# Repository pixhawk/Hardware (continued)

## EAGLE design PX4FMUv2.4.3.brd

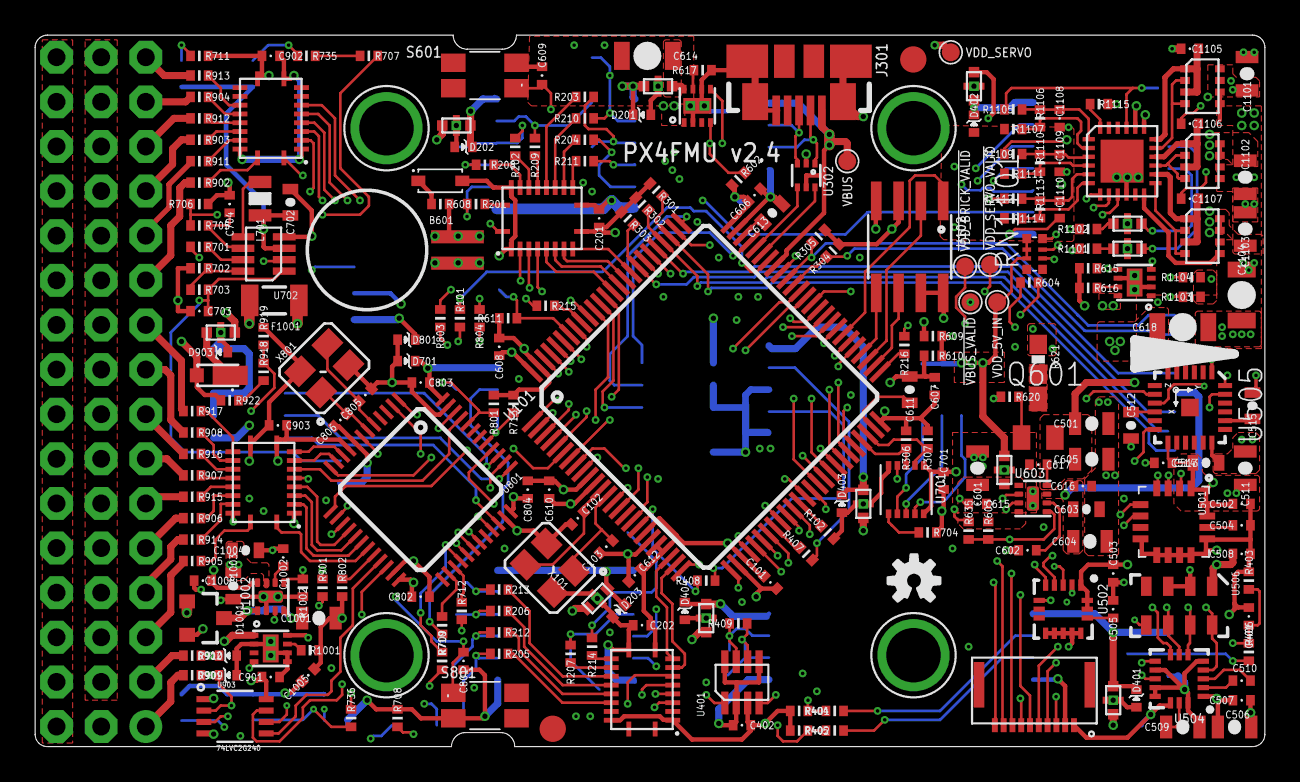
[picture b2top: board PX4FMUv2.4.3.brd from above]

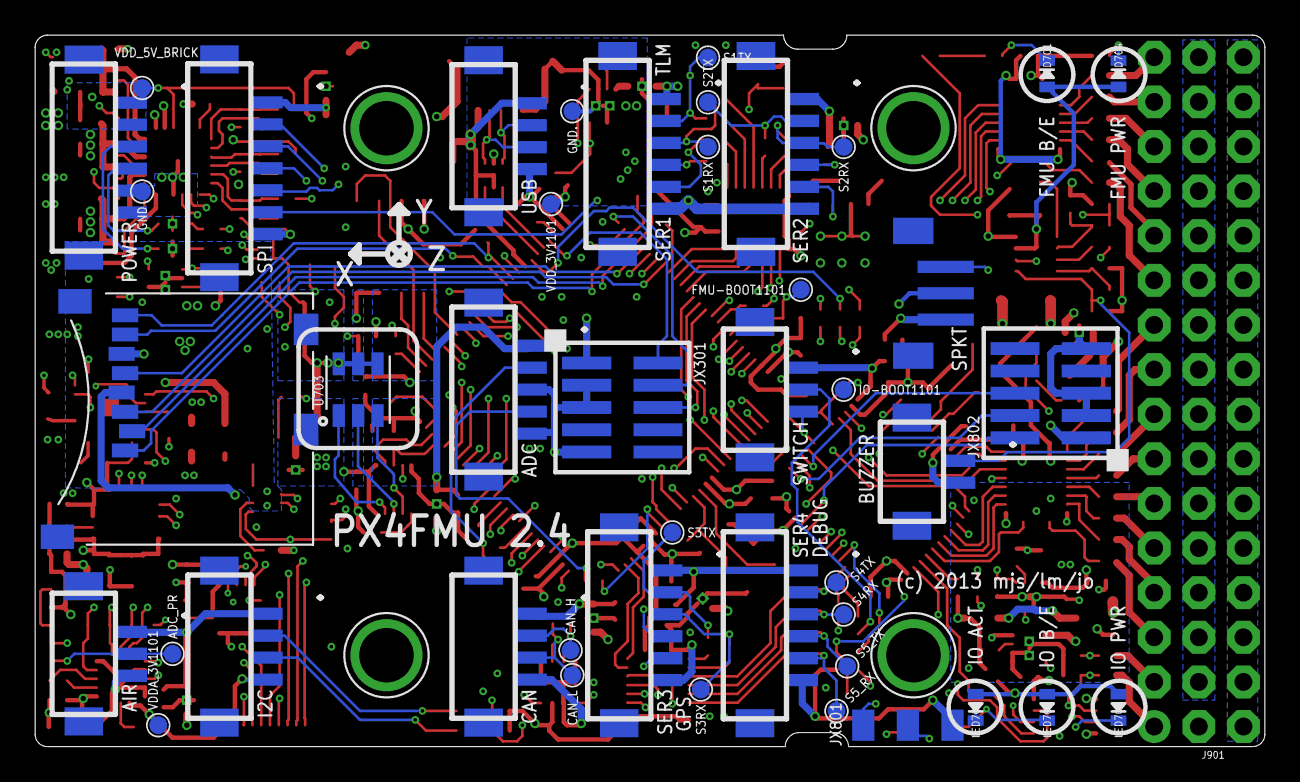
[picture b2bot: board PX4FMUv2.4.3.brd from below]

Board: 6 copper layers, 70.0 x 40.5 mm, 292 parts (45 on the bottom side), 262 nets.

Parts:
!VBUS_VALID: PAD.04; PAD.04X.04
!VDD_BRICK_VALID: PAD.04; PAD.04X.04
!VDD_SERVO_VALID: PAD.04; PAD.04X.04
ADC_PR: PAD.04; PAD.04X.04
B601: MS621FE
C101, C201, C202, C401, C402, C502, C503, C507, C508, C514, C606, C607, C608, C609, C610, C612, C615, C616, C617, C701, C801, C802, C803, C804, C901, C902, C903, C1005, C1105, C1106, C1107: 0u1; 0402-CAP
C102, C103, C805, C806: 8p; 0402-CAP
C501, C506, C509, C511: 10u/10V; 0805-CAP
C504, C505, C602, C1002: 10n; 0402-CAP
C510, C704: 0u47; 0402-CAP
C512, C513, C611, C613: 2u2; 0603-CAP
C515: 0u01; 0603-CAP
C601, C1001: 10u/25V; 0805-CAP
C603, C702, C1003: 1u; 0603-CAP
C604, C605, C1101, C1102, C1103: 22u/25V; 0805-CAP
C614, C618, C1104: 100u; 1206-CAP
C703: 5n6; 0402-CAP
C1004: 10u; 0603-CAP
C1008: 2u2; 0402-CAP
C1108, C1109, C1110: 1000p/25V; 0402-CAP
CAN_H: PAD.04; PAD.04X.04
CAN_L: PAD.04; PAD.04X.04
D201, D202, D203, D401, D402, D403, D404, D701, D801, D901, D902, D903: PESD0402-140; 0402-TVS
D602: RB751V40T1G; SOD323
D904: MSS1P4-M3; MICROSMP
D1001: PMEG2005CT; SOT23-3
F1001: 0ZCA0035FF2G; PTC-1206
FMU-BOOT1101: PAD.04; PAD.04X.04
GND, GND.: PAD.04; PAD.04X.04
IO-BOOT1101: PAD.04; PAD.04X.04
J201, J202, J203, J204, J601: DF13C-6P-1.25V
J301: 47346-0001; MOLEX-47346-0001
J302, J401, J405: DF13C-4P-1.25V
J402, J702: DF13C-3P-1.25V
J403: DF13C-7P-1.25V
J404: DF13C-5P-1.25V
J701: DF13C-2P-1.25V
J801: JST-ZH-3; JST-ZH-SMT-VERTICAL
J901: 3X16RA
JP1, JP2: FIDUCIAL1.5X3; FIDUCIAL-1.5X3
JX301, JX802: ARM_MINI_JTAG-SMT; FTSH-105-01-XXX-DV-K
JX801: HEADER-3X1BOARDEDGE-SHORT; HEADER_3X01_SMD_H_BOARD_EDGE_SHORT
L201, L202, L203, L401, L402, L403, L404, L603, L901, L1101, L1102: KNH16C104DA5TS; KYOCERA-KNH16-DA
L701: 47uH; 0805-IND
LED701, LED703: AMBER; 0603-LED
LED702, LED704: GREEN; 0603-LED
LED705: BLUE; 0603-LED
M3_MOUNT1101, M3_MOUNT1102, M3_MOUNT1103, M3_MOUNT1104: MOUNT-HOLE3.1MM; MOUNT-HOLE3.1
OSHW_LOGO: OSHW-LOGOS; OSHW-LOGO-S
Q601: MMBT3906LT1SMD; SOT23-BEC
R101: 470R; 0402-RES
R102, R603, R611, R615, R702, R704, R801, R802, R901, R1002: 10K; 0402-RES
R201, R202, R203, R204, R205, R206, R207, R208, R209, R210, R211, R212, R213, R214, R215, R216, R404, R405, R409: 120R; 0402-RES
R301, R302, R303, R304, R305, R703, R1001: 100K; 0402-RES
R306, R307, R401, R402, R713: 1K5; 0402-RES
R403, R406, R407, R408, R609, R610, R918, R919, R922, R1101, R1102: 10K/0.1%; 0402-RES
R602, R604, R1103, R1104: 1M; 0402-RES
R608: 1K; 0402-RES
R616: 25K5; 0402-RES
R617, R706: 16K5; 0402-RES
R620: 1K8; 0402-RES
R621: 10R; 0603-RES
R635: DNP/10K; 0402-RES
R701: 9K09; 0402-RES
R705, R1105, R1109, R1112: 453K; 0402-RES
R707, R708, R709, R711, R712, R735, R736, R803, R804, R902, R903, R904, R905, R906, R907, R908, R909, R910, R911, R912, R913, R914, R915, R916, R917: 220R; 0402-RES
R710: 68R; 0402-RES
R1106, R1110, R1113: 56K; 0402-RES
R1107, R1111, R1114: 105K; 0402-RES
R1115: 0R; 0402-RES
RN1101: 1M; EXB28V
S1RX, S1TX, S2RX, S2TX, S3RX, S3TX, S4RX, S4TX, S5_RX, S5_TX: PAD.04; PAD.04X.04
S601, S801: RESET; EVQP7J01K
U101: STM32F4X7VX; TQFP100
U102: FM25V01; SO08
U201, U202, U901, U902: TXS0108QFN20; QFN20-RGY
U301: 2908-05WB-MG; MICROSD
U302: NUF2042XV6; SOT563-6
U401: MAX3051; SOT23-8
U501: L3GD20; L3G4200DH-MAN
U502: L3GD20H; LGA-16L
U504: LSM303D; LGA-16L
U505: MPU-6000; QFN-24
U506: MS5611-01BA
U601, U602: BQ24315; QFN8-DSG
U603, U1002: MIC5332; MLF-8-EPAD
U701: TCA62724FMG; SON10
U702: LT3469; SOT23-8
U703: LRTB GFTG-T7AW-1+V7A7-29+R5T9-49-L; 6-PLCC
U801: STM32F10XCXT6; TQFP48
U903: 74LVC2G240; TSSOP8_SOT505-2
U1001: BQ24313; QFN8-DSG
U1101: LTC4417; MO-220
U1102, U1103, U1104: NTHD4102PT1G; 1206-8
VBUS: PAD.04; PAD.04X.04
VDDA_3V1101: PAD.04; PAD.04X.04
VDD_3V1101, VDD_5V_BRICK, VDD_5V_IN: PAD.04; PAD.04X.04
VDD_SERVO: PAD.04; PAD.04X.04
X101, X801: 3.2x2.5 mm / 24 MHz / 15 ppm; OSCILLATOR-3.2X2.5
X503: 0512811094; 51281-1094

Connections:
!ACCEL_MAG_CS: U101.9, U504.8, X503.6
!BARO_CS: U101.88, U506.5
!FMU-LED_AMBER: R707.P$1, U101.43
!FRAM_CS: U101.57, U102.1
!GYRO_CS: U101.7, U501.5, U502.5, X503.7
!IO-LED_AMBER: R709.P$1, U801.28
!IO-LED_BLUE: R712.P$1, U801.27
!IO-LED_SAFETY: R710.P$2, U801.26
!MPU_CS: U101.17, U505.8
!SBUS_OUTPUT_EN: U801.40, U903.7
!SPI_EXT_NSS: J403.5, U101.3
!VBUS_VALID: !VBUS_VALID.P$1, RN1101.2, U101.15, U1101.P$9
!VDD_5V_HIPOWER_OC: R602.P$1, U101.41, U601.4
!VDD_5V_PERIPH_EN: R615.P$1, U101.67, U601.5, U602.5
!VDD_5V_PERIPH_OC: R604.P$1, U101.46, U602.4
!VDD_BRICK_VALID: !VDD_BRICK_VALID.P$1, RN1101.4, U101.91, U1101.P$7
!VDD_SERVO_VALID: !VDD_SERVO_VALID.P$1, RN1101.3, U101.93, U1101.P$8
ACCEL_DRDY: U101.90, U504.11, X503.3
ALARM: R701.P$2, U101.77
BATT_CURRENT_SENS: R1101.P$1, U101.26
BATT_CURRENT_SENS_PROT: J601.3, L1101.P$1, R1104.P$1
BATT_VOLTAGE_SENS: R1102.P$1, U101.25
BATT_VOLTAGE_SENS_PROT: J601.4, L1102.P$1, R1103.P$1
CAN1_RX: U101.81, U401.4
CAN1_TX: U101.82, U401.1
CAN2_RX: R216.P$1, U101.51
CAN2_TX: R215.P$1, U101.92
CAN_H: CAN_H.P$1, J405.2, R409.P$1, U401.7
CAN_L: CAN_L.P$1, J405.3, R409.P$2, U401.6
FMU-!RESET: C609.P$2, R635.P$1, S601.A1, U101.14, U603.3, U701.4
FMU-BOOT0: FMU-BOOT1101.P$1, R611.P$2, U101.94
FMU-CH1: U101.45, U901.7
FMU-CH1-PROT: J901.46, R913.P$2
FMU-CH2: U101.44, U901.6
FMU-CH3: U101.42, U901.5
FMU-CH4: U101.40, U901.4
FMU-CH5: U101.60, U901.3
FMU-CH6: U101.61, U901.1
FMU-CH6-PROT: J901.31, R902.P$2
FMU-I2C1_SCL: R401.P$1, R404.P$1, U101.95
FMU-I2C1_SDA: R402.P$1, R405.P$1, U101.96
FMU-I2C2_SCL: R306.P$1, U101.47, U701.3
FMU-I2C2_SDA: R307.P$1, U101.48, U701.2
FMU-SWCLK: JX301.4, U101.76
FMU-SWDIO: JX301.2, U101.72
FMU-SWO: JX301.6, U101.89
FMU-UART4_RX: U101.24, U202.8
FMU-UART4_TX: U101.23, U202.9
FMU-UART7_RX: U101.38, U202.4
FMU-UART7_TX: U101.39, U202.5
FMU-UART8_RX: U101.97, U202.6
FMU-UART8_TX: U101.98, U202.7
FMU-USART2_CTS: U101.84, U201.9
FMU-USART2_RTS: U101.85, U201.8
FMU-USART2_RX: U101.87, U201.6
FMU-USART2_TX: U101.86, U201.7
FMU-USART3_CTS: U101.58, U201.3
FMU-USART3_RTS: U101.59, U201.1
FMU-USART3_RX: U101.56, U201.4
FMU-USART3_TX: U101.55, U201.5
FMU-VDD_3V3: C101.P$1, C201.P$1, C202.P$1, C402.P$1, C603.P$1, C604.P$1, C606.P$1, C607.P$1, C608.P$1, C610.P$1, C612.P$1, C616.P$1, C701.P$1, C902.P$1, D602.A, JX301.1, R301.P$2, R302.P$2, R303.P$2, R304.P$2, R305.P$2, R306.P$2, R307.P$2, R401.P$2, R402.P$2, R602.P$2, R604.P$2, U101.11, U101.19, U101.21, U101.22, U101.28, U101.50, U101.75, U101.100, U102.3, U102.7, U102.8, U201.2, U201.10, U201.19, U202.2, U202.10, U202.19, U301.4, U401.3, U603.7, U701.1, U701.10, U901.2, U901.10, U901.19, VDD_3V1101.P$1
FMU-VDD_5V5: C601.P$1, C615.P$1, L603.P$2, R603.P$1, U603.1, U603.4
FMU_AUX_ADC1: R408.P$1, U101.18
FMU_AUX_ADC1_PROT: J404.4, R408.P$2
FMU_AUX_ADC2: R407.P$1, U101.33
FMU_AUX_ADC2_PROT: J404.2, R407.P$2
FRAM_MISO: U101.53, U102.2
FRAM_MOSI: U101.54, U102.5
FRAM_SCK: U101.52, U102.6
GND: B601.2, C101.P$2, C102.P$2, C103.P$1, C201.P$2, C202.P$2, C401.P$2, C402.P$2, C501.P$2, C502.P$2, C503.P$2, C504.P$2, C505.P$2, C506.P$2, C507.P$2, C508.P$2, C509.P$2, C511.P$2, C512.P$2, C513.P$2, C514.P$2, C515.P$2, C601.P$2, C602.P$1, C603.P$2, C604.P$2, C605.P$2, C606.P$2, C607.P$2, C608.P$2, C609.P$1, C610.P$2, C611.P$2, C612.P$2, C613.P$2, C614.P$2, C615.P$2, C616.P$2, C617.P$2, C618.P$2, C701.P$2, C702.P$2, C703.P$2, C704.P$2, C801.P$1, C802.P$2, C803.P$2, C804.P$2, C805.P$2, C806.P$1, C901.P$2, C902.P$2, C903.P$2, C1001.P$2, C1002.P$2, C1003.P$2, C1004.P$2, C1005.P$2, C1008.P$2, C1101.P$2, C1102.P$2, C1103.P$2, C1104.P$2, C1105.P$2, C1106.P$2, C1107.P$2, C1108.P$2, C1109.P$2, C1110.P$2, D201.A, D202.A, D203.A, D401.A, D402.A, D403.A, D404.A, D701.A, D801.A, D901.A, D902.A, D903.A, GND.P$1, GND..P$1, J201.6, J202.6, J203.6, J204.6, J301.GND, J301.GND1, J301.GND2, J301.GND3, J301.GND4, J302.4, J401.4, J402.3, J403.7, J404.3, J404.5, J405.4, J601.5, J601.6, J701.2, J801.P$2, J901.3, J901.6, J901.9, J901.12, J901.15, J901.18, J901.21, J901.24, J901.27, J901.30, J901.33, J901.36, J901.39, J901.42, J901.45, J901.48, JX301.3, JX301.5, JX301.9, JX801.3, JX802.3, JX802.5, JX802.9, L201.P$3, L201.P$4, L201.P$5, L202.P$3, L202.P$4, L202.P$5, L203.P$3, L203.P$4, L203.P$5, L401.P$3, L401.P$4, L401.P$5, L402.P$3, L402.P$4, L402.P$5, L403.P$3, L403.P$4, L403.P$5, L404.P$3, L404.P$4, L404.P$5, L603.P$3, L603.P$4, L603.P$5, L901.P$3, L901.P$4, L901.P$5, L1101.P$3, L1101.P$4, L1101.P$5, L1102.P$3, L1102.P$4, L1102.P$5, R102.P$2, R403.P$1, R610.P$2, R611.P$1, R615.P$2, R616.P$2, R617.P$2, R621.1, R702.P$2, R704.P$1, R706.P$2, R708.P$1, R711.P$1, R713.P$2, R801.P$2, R802.P$2, R919.P$1, R1001.P$1, R1002.P$1, R1103.P$2, R1104.P$2, R1107.P$2, R1111.P$2, R1114.P$2, R1115.P$1, S601.B3, S801.B3, U101.10, U101.20, U101.27, U101.74, U101.99, U102.4, U201.11, U202.11, U301.6, U302.2, U401.2, U401.5, U401.8, U501.8, U501.9, U501.10, U501.11, U501.12, U501.13, U502.9, U502.10, U502.11, U502.12, U502.13, U504.5, U504.10, U504.12, U504.13, U504.16, U505.1, U505.18, U506.2, U506.3, U601.2, U601.6, U601.GND, U601.P$2, U601.P$3, U602.2, U602.6, U602.GND, U602.P$2, U602.P$3, U603.2, U603.GND, U701.5, U702.4, U801.8, U801.23, U801.35, U801.47, U901.11, U902.11, U903.1, U903.4, U1001.2, U1001.5, U1001.6, U1001.GND, U1001.P$2, U1001.P$3, U1002.2, U1002.GND, U1101.P$10, U1101.P$25, X101.2, X101.4, X503.2, X801.2, X801.4
GPIO_EXT_1: J403.6, U101.8
GYRO_DRDY: U101.35, U501.6, U502.6, X503.5
IO-!RESET: C801.P$2, S801.A1, U801.7, U1002.3
IO-!VDD_SERVO_IN_FAULT: U801.38, U1001.4
IO-BOOT0: IO-BOOT1101.P$1, R801.P$1, U801.44
IO-BOOT1: R802.P$1, U801.20
IO-CH1: U801.10, U902.9
IO-CH1-PROT: J901.28, R917.P$2
IO-CH2: U801.11, U902.8
IO-CH3: U801.45, U902.7
IO-CH4: U801.46, U902.6
IO-CH5: U801.16, U902.5
IO-CH6: U801.17, U902.4
IO-CH7: U801.18, U902.3
IO-CH8: U801.19, U902.1
IO-CH8-PROT: J901.7, R905.P$2
IO-SWCLK: JX802.4, U801.37
IO-SWDIO: JX802.2, U801.34
IO-SWO: JX802.6, U801.39
IO-USART1_RX: J801.P$3, JX801.2, U801.31
IO-USART1_TX: JX801.1, R101.P$2, U801.30
IO-VDD_3V3: C802.P$1, C803.P$1, C804.P$1, C901.P$1, C903.P$1, C1003.P$1, C1004.P$1, D701.C, J702.1, JX802.1, U801.9, U801.24, U801.36, U801.48, U902.2, U902.10, U902.19, U903.8, U1002.7
IO-VDD_5V5: C1001.P$1, C1005.P$1, D1001.3, J901.2, LED702.A, LED703.A, LED705.A, U1002.1, U1002.4
MAG_DRDY: U101.36, U504.9, X503.4
MPU_DRDY: U101.62, U505.12
unnamed: C103.P$2, U101.13, X101.1
unnamed: C102.P$1, U101.12, X101.3
unnamed: R918.P$2, R922.P$1
unnamed: D1001.2, U1001.8
unnamed: D201.C, J201.1, L201.P$2
unnamed: C509.P$1, U504.15
unnamed: LED704.C, R711.P$2
unnamed: C613.P$1, U101.73
unnamed: LED705.C, R712.P$2
unnamed: C510.P$1, U504.2
unnamed: C602.P$2, U603.6
unnamed: C611.P$1, U101.49
unnamed: R707.P$2, R735.P$1
unnamed: J203.4, R215.P$2
unnamed: R803.P$1, U801.12
unnamed: R804.P$1, U801.13
unnamed: C510.P$2, U504.3
unnamed: C806.P$2, U801.6, X801.1
unnamed: J203.5, R216.P$2
unnamed: R1001.P$2, U1001.7
unnamed: D602.C, R608.P$2
unnamed: C805.P$1, U801.5, X801.3
unnamed: R101.P$1, U101.69
unnamed: R705.P$2, R706.P$1, U702.2
unnamed: R702.P$1, R703.P$2, U702.8
unnamed: LED701.C, R735.P$2
unnamed: C703.P$1, J701.1, R703.P$1, U702.1
unnamed: R701.P$1, U702.7
unnamed: LED702.C, R708.P$2
unnamed: C505.P$1, U502.14
unnamed: J901.10, R914.P$2
unnamed: L701.P$2, U702.5
unnamed: J401.2, R404.P$2
unnamed: R616.P$1, U602.7
unnamed: C504.P$1, U501.14
unnamed: C704.P$1, R705.P$1, U702.6
unnamed: J401.3, R405.P$2
unnamed: D902.C, R901.P$2, R910.P$1, U903.3
unnamed: R709.P$2, R736.P$1
unnamed: LED703.C, R736.P$2
unnamed: D402.C, J403.1, L402.P$2
unnamed: D401.C, J401.1, J402.1, L401.P$2
unnamed: R905.P$1, U902.20
unnamed: R914.P$1, U902.18
unnamed: R906.P$1, U902.17
unnamed: D1001.1, F1001.2
unnamed: C1108.P$1, R1105.P$2, R1106.P$1, U1101.P$1
unnamed: D404.C, J405.1, L403.P$2
unnamed: R915.P$1, U902.16
unnamed: C512.P$1, U505.10
unnamed: C515.P$1, U505.20
unnamed: R907.P$1, U902.15
unnamed: R1106.P$2, R1107.P$1, U1101.P$2
unnamed: C1109.P$1, R1109.P$2, R1110.P$1, U1101.P$3
unnamed: R1110.P$2, R1111.P$1, U1101.P$4
unnamed: J702.2, R710.P$1
unnamed: R916.P$1, U902.14
unnamed: R908.P$1, U902.13
unnamed: R917.P$1, U902.12
unnamed: R902.P$1, U901.20
unnamed: R911.P$1, U901.18
unnamed: R903.P$1, U901.17
unnamed: R912.P$1, U901.16
unnamed: R904.P$1, U901.15
unnamed: R913.P$1, U901.14
unnamed: R1113.P$2, R1114.P$1, U1101.P$6
unnamed: J901.34, R911.P$2
unnamed: C1110.P$1, R1112.P$2, R1113.P$1, U1101.P$5
unnamed: R201.P$1, U201.20
unnamed: J901.13, R906.P$2
unnamed: J901.16, R915.P$2
unnamed: J901.19, R907.P$2
unnamed: J901.22, R916.P$2
unnamed: J901.25, R908.P$2
unnamed: J901.37, R903.P$2
unnamed: J901.40, R912.P$2
unnamed: J901.43, R904.P$2
unnamed: Q601.C, R621.2
unnamed: Q601.B, R620.P$1
unnamed: R208.P$1, U201.18
unnamed: R202.P$1, U201.17
unnamed: R209.P$1, U201.16
unnamed: R203.P$1, U201.15
unnamed: R210.P$1, U201.14
unnamed: R204.P$1, U201.13
unnamed: R211.P$1, U201.12
unnamed: R207.P$1, U202.13
unnamed: R214.P$1, U202.12
unnamed: R205.P$1, U202.17
unnamed: R212.P$1, U202.16
unnamed: R206.P$1, U202.15
unnamed: R213.P$1, U202.14
unnamed: R704.P$2, U701.6
unnamed: R617.P$1, U601.7
unnamed: C1105.P$1, U1101.P$18, U1102.P$1, U1102.P$3
unnamed: D403.C, J404.1, L404.P$2
unnamed: J901.4, R910.P$2
unnamed: D203.C, J203.1, J204.1, L203.P$2
unnamed: D202.C, J202.1, L202.P$2
unnamed: L1102.P$2, R1102.P$2
unnamed: L1101.P$2, R1101.P$2
unnamed: C1002.P$1, U1002.6
unnamed: R1115.P$2, U1101.P$24
unnamed: C1106.P$1, U1101.P$16, U1103.P$1, U1103.P$3
unnamed: C1107.P$1, U1101.P$14, U1104.P$1, U1104.P$3
unnamed: U1101.P$13, U1104.P$2, U1104.P$4
unnamed: D903.C, D904.CATHODE, L901.P$1
unnamed: U1101.P$15, U1103.P$2, U1103.P$4
unnamed: U1101.P$17, U1102.P$2, U1102.P$4
OTG_DM1: J301.D-, J302.3, U302.1
OTG_DP1: J301.D+, J302.2, U302.3
OTG_FS_DM: U101.70, U302.6
OTG_FS_DP: U101.71, U302.4
PB2-BOOT1: R102.P$1, U101.37
PPM-SBUS-PROT: J901.1, R909.P$2
PPM_INPUT: D901.C, R909.P$1, U801.29, U903.2
PRESSURE_SENS: C401.P$1, R403.P$2, R406.P$1, U101.34
PRESSURE_SENS_IN: ADC_PR.P$1, J402.2, R406.P$2
RGB_LED_3: U701.9, U703.C1
RGB_LED_4: U701.8, U703.C2
RGB_LED_14: U701.7, U703.C3
RSSI_IN: R901.P$1, U801.15, U801.33
SAFETY: J702.3, R713.P$1, U801.41
SBUS_INPUT: U801.22, U903.6
SBUS_OUTPUT: U801.21, U903.5
SDIO_CK: U101.80, U301.5
SDIO_CMD: R303.P$1, U101.83, U301.3
SDIO_D0: R304.P$1, U101.65, U301.7
SDIO_D1: R305.P$1, U101.66, U301.8
SDIO_D2: R301.P$1, U101.78, U301.1
SDIO_D3: R302.P$1, U101.79, U301.2
SERIAL1_CTS: J201.4, R211.P$2
SERIAL1_RTS: J201.5, R204.P$2
SERIAL1_RX: J201.3, R203.P$2, S1RX.P$1
SERIAL1_TX: J201.2, R210.P$2, S1TX.P$1
SERIAL2_CTS: J202.4, R208.P$2
SERIAL2_RTS: J202.5, R201.P$2
SERIAL2_RX: J202.3, R202.P$2, S2RX.P$1
SERIAL2_TX: J202.2, R209.P$2, S2TX.P$1
SERIAL3_RX: J203.3, R207.P$2, S3RX.P$1
SERIAL3_TX: J203.2, R214.P$2, S3TX.P$1
SERIAL4_RX: J204.3, R206.P$2, S4RX.P$1
SERIAL4_TX: J204.2, R213.P$2, S4TX.P$1
SERIAL5_RX: J204.5, R205.P$2, S5_RX.P$1
SERIAL5_TX: J204.4, R212.P$2, S5_TX.P$1
SERIAL_FMU_TO_IO: R804.P$2, U101.63
SERIAL_IO_TO_FMU: R803.P$2, U101.64
SPI_EXT_MISO: J403.3, U101.4
SPI_EXT_MOSI: J403.4, U101.5
SPI_EXT_SCK: J403.2, U101.1
SPI_INT_MISO: U101.31, U501.4, U502.4, U504.7, U505.9, U506.6, X503.9
SPI_INT_MOSI: U101.32, U501.3, U502.3, U504.6, U505.24, U506.7, X503.8
SPI_INT_SCK: U101.30, U501.2, U502.2, U504.4, U505.23, U506.8, X503.10
VBAT: B601.1, R608.P$1, U101.6, U801.1
VBUS: C1103.P$1, J301.VBUS, J302.1, R1112.P$1, U101.68, U302.5, U1101.P$19, U1104.P$7, U1104.P$8, VBUS.P$1
VDD_3V3_SENSORS: C501.P$1, C502.P$1, C503.P$1, C506.P$1, C507.P$1, C508.P$1, C511.P$1, C513.P$1, C514.P$1, C605.P$1, C617.P$1, Q601.E, U501.1, U501.15, U501.16, U502.1, U502.15, U502.16, U504.1, U504.14, U505.13, U506.1, U603.8, VDDA_3V1101.P$1, X503.1
VDD_3V3_SENSORS_EN: R603.P$2, R620.P$2, R635.P$2, U101.2, U603.5
VDD_3V3_SPEKTRUM: C1008.P$1, D801.C, J801.P$1, U1002.8
VDD_3V3_SPEKTRUM_EN: R1002.P$2, U801.2, U1002.5
VDD_5V_BRICK: C1101.P$1, J601.1, J601.2, R1105.P$1, U1101.P$21, U1102.P$7, U1102.P$8, VDD_5V_BRICK.P$1
VDD_5V_HIPOWER: C614.P$1, L201.P$1, U601.8
VDD_5V_IN: C702.P$1, C1104.P$1, F1001.1, L603.P$1, L701.P$1, LED701.A, LED704.A, R609.P$2, RN1101.5, RN1101.6, RN1101.7, U601.1, U602.1, U702.3, U703.A1, U703.A2, U703.A3, U1101.P$12, U1102.P$5, U1102.P$6, U1103.P$5, U1103.P$6, U1104.P$5, U1104.P$6, VDD_5V_IN.P$1
VDD_5V_PERIPH: C618.P$1, L202.P$1, L203.P$1, L401.P$1, L402.P$1, L403.P$1, L404.P$1, U602.8
VDD_5V_SENS: R609.P$1, R610.P$1, U101.29
VDD_SERVO: C1102.P$1, D904.ANODE, J901.5, J901.8, J901.11, J901.14, J901.17, J901.20, J901.23, J901.26, J901.29, J901.32, J901.35, J901.38, J901.41, J901.44, J901.47, R922.P$2, R1109.P$1, U1101.P$20, U1103.P$7, U1103.P$8, VDD_SERVO.P$1
VDD_SERVO_IN: L901.P$2, U1001.1
VDD_SERVO_SENS: R918.P$1, R919.P$2, U801.14

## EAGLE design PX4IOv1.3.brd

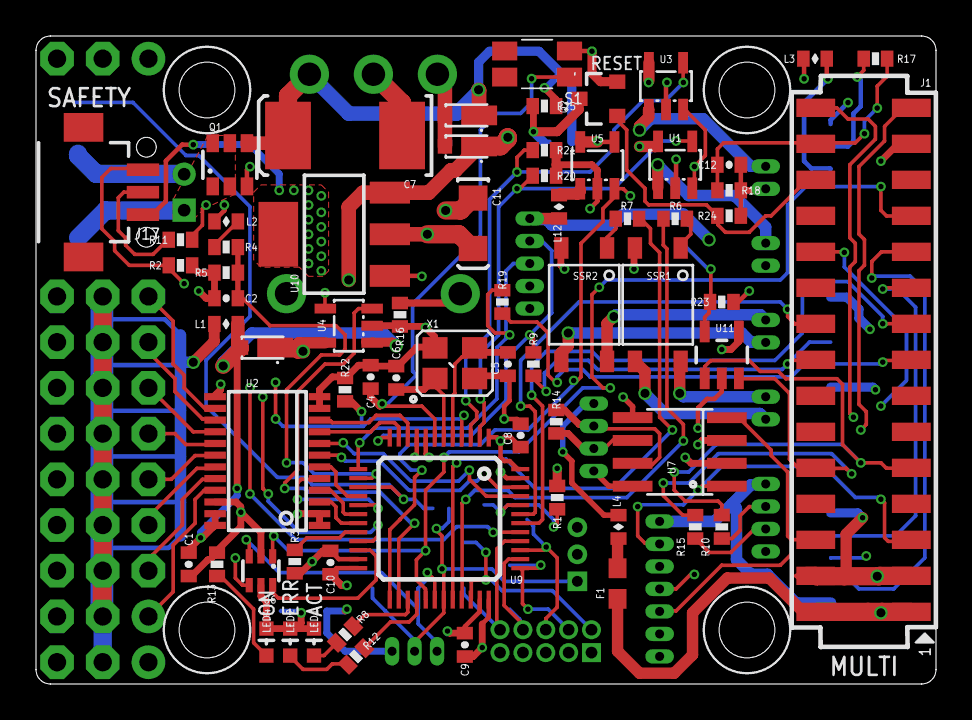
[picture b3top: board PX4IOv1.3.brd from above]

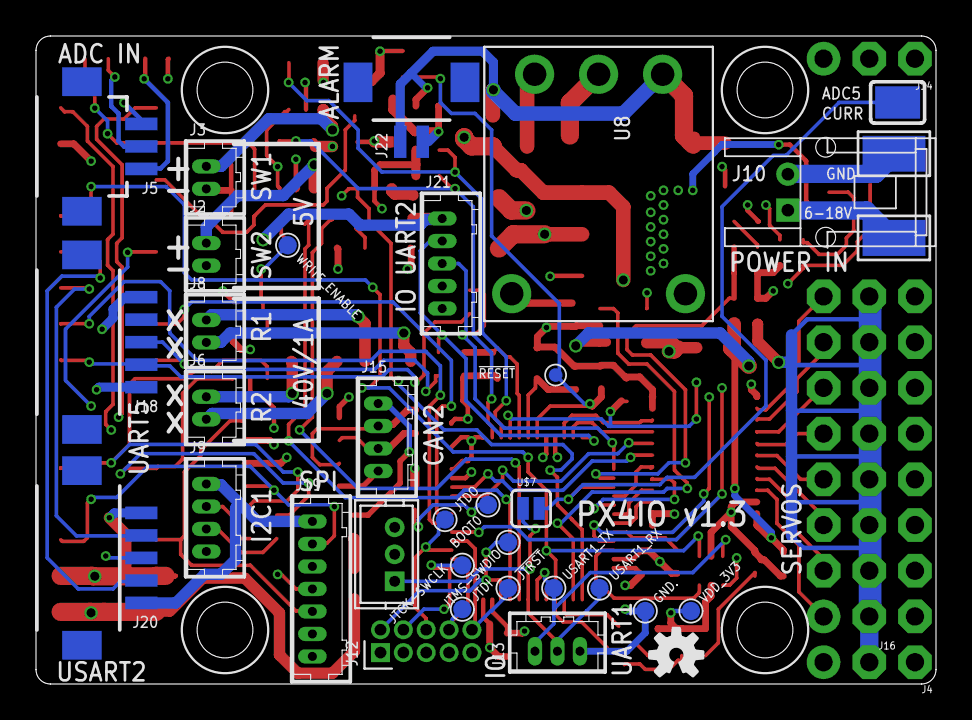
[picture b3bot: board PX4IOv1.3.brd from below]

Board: 4 copper layers, 50.0 x 36.0 mm, 107 parts (37 on the bottom side), 95 nets.

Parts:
6-18V: 3,5-2
!JTRST: PAD.04; PAD.04X.04
!RESET: PAD.03; PAD.03X.03
BOOT0: PAD.04; PAD.04X.04
C1, C2, C4, C8, C9, C10, C12: 0u1; 0402-CAP
C5, C6: 8p; 0402-CAP
C7: 100u; EIA7343
C11: 4u7; EIA3216
D1, D2: BAT 60A E6327; MICROSMP
D3: MSS1P4-M3/89A; MICROSMP
F1: 500mA; 0603
GND: 3,5-2
GND.: PAD.04; PAD.04X.04
J1: HEADER_2X15-REV; HEADER_2MM_2X15_REVERSE
J2, J3, J6, J8: DF13-2P-1.25DSA
J4, J14: HEADER-3X1; 3X1RA
J5: DF13-3P-1.25H; DF13A-3P-1.25H
J7: CONN_SPEKTRUM_RX-TH; B3B-ZR
J9, J15: DF13-4P-1.25DSA
J10: JST-PA-02; S02B-PASK-2
J12: ARM_MINI_JTAG-TH; FTSH-105-01-XXX-DV
J13: DF13-3P-1.25DSA
J16: HEADER-3X8SERVO; 3X8RA
J17: DF13A-3P-1.25H
J18, J20: DF13-5P-1.25H; DF13A-5P-1.25H
J19: DF13-7P-1.25DSA
J21: DF13-5P-1.25DSA
J22: DF13-2P-1.25H; DF13A-2P-1.25H
JTCK-SWCLK: PAD.04; PAD.04X.04
JTDI: PAD.04; PAD.04X.04
JTDO: PAD.04; PAD.04X.04
JTMS-SWDIO: PAD.04; PAD.04X.04
L1, L2, L3, L4, L12: FERRITE; 0402-IND
LED1: BLUE; LED-0603
LED2: AMBER; LED-0603
LED4: GREEN; LED-0603
PAD1: ADC_IN5; PAD-2.5-1.8
Q1: NTGS4111P; TSOP-6@1
Q2: MOSFET-NCHANNELSMD; SOT23-3
R1, R3, R23, R24, R25: 10K; 0402-RES
R2, R20, R21, R22: 4K7; 0402-RES
R4: 47K/0.1%; 0402-RES
R5, R17, R18: 10K/0.1%; 0402-RES
R6, R7: 470R; 0402-RES
R8: 82R; 0402-RES
R9, R19: DNP; 0402-RES
R10, R15: 100R; 0402-RES
R11: 47R; 0402-RES
R12, R13: 270R; 0402-RES
R14: 120R; 0402-RES
R16: 205R/1%/100ppm; 0402-RES
S1: RESET; EVQP7J01K
SSR1, SSR2: TLP3123(F); SOP4-2.54
U1, U3, U5: TPS2051B / AP2151WG-7 / STMPS2151STR; SOT23-5L
U2: SN74LVC8T245; R-PDSO-G24
U4: TPS2061B / STMPS2171STR; SOT23-5L
U6: 74LVC2GU04; SOT363_PHILIPS
U7: MAX3051; SO08
U8: PTH08080WAH; PTH08080W_TH
U9: STM32F10XCXT6; TQFP48
U10: LD1117AS33; SOT-223
U11: EEPROM-I2C-SOT23-5; SOT23-5
U$1: OSHW-LOGOS; OSHW-LOGO-S
U$2, U$3, U$4, U$5: MOUNT-HOLE3.1MM; MOUNT-HOLE3.1
U$7: JUMPER-2; SJ_2
USART1_RX, USART1_TX: PAD.04; PAD.04X.04
VDD_3V3: PAD.04; PAD.04X.04
WRITE_ENABLE: PAD.04; PAD.04X.04
X1: 3.2x2.5 mm / 24 MHz / 15 ppm; OSCILLATOR-3.2X2.5

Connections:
!JTRESET: !JTRST.P$1, J12.10, U9.40
ACC1_PWR_EN: R20.2, U1.4, U9.2
ACC2_PWR_EN: R21.2, U3.4, U9.3
ACC_OC_DETECT: U1.3, U3.3, U5.3, U9.25
ACC_POWER_5V: J9.1, J18.1, J19.1, J20.1, J21.1, L12.2
ADC1_IN4: C2.1, R4.1, R5.2, U9.14
ADC1_IN5: PAD1.P$1, U9.15, U$7.2
BOOT0: BOOT0.P$1, R1.1, U9.44
CH1: U2.10, U9.10
CH2: U2.9, U9.11
CH3: U2.8, U9.45
CH4: U2.7, U9.46
CH5: U2.6, U9.16
CH6: U2.5, U9.17
CH7: U2.4, U9.18
CH8: U2.3, U9.19
FMU_ALARM: J1.26, Q2.1, R24.1
FMU_ANALOG1: C12.1, J1.28, R17.1, R18.2
FMU_ANALOG2: J1.29, J19.3
FMU_ANALOG3: J1.30, J19.4
FMU_CAN2_RX: J1.6, J19.5, U7.4
FMU_CAN2_TX: J1.5, J19.2, U7.1
FMU_I2C2_SCL: J1.17, U9.42
FMU_I2C2_SDA: J1.18, U9.43
FMU_I2C3_SCL: J1.9, R10.1, U11.1
FMU_I2C3_SDA: J1.10, R15.1, U11.3
FMU_UART5_RX: J1.16, J18.3, R9.2
FMU_UART5_TX: J1.15, J18.2, R19.2
FMU_USART2_CTS: J1.19, J20.4
FMU_USART2_RX: J1.22, J20.3
FMU_USART2_TX: J1.21, J20.2
GND: C1.2, C2.2, C4.2, C5.2, C6.1, C7.C, C8.2, C9.2, C10.2, C11.C, C12.2, GND.1, GND..P$1, J1.3, J1.4, J1.27, J2.2, J3.2, J4.3, J5.3, J7.2, J9.4, J10.2, J12.3, J12.5, J12.9, J13.3, J14.3, J15.4, J16.3, J16.6, J16.9, J16.12, J16.15, J16.18, J16.21, J16.24, J18.5, J19.7, J20.5, J21.5, Q1.3, Q2.2, R1.2, R2.2, R3.2, R5.1, R13.1, R16.1, R18.1, R20.1, R21.1, R22.1, R23.2, R24.2, S1.B3, SSR1.2, SSR2.2, U1.2, U2.11, U2.12, U2.13, U2.22, U3.2, U4.2, U5.2, U6.2, U7.2, U7.5, U7.8, U8.2, U9.8, U9.23, U9.35, U9.47, U10.1, U11.2, X1.2, X1.4
JTCK-SWCLK: J12.4, JTCK-SWCLK.P$1, U9.37
JTDI: J12.8, JTDI.P$1, U9.38
JTDO: J12.6, JTDO.P$1, U9.39
JTMS-SWDIO: J12.2, JTMS-SWDIO.P$1, U9.34
LED1: R8.1, U9.27
LED2: R12.1, U9.28
LED3: R11.2, U9.21
unnamed: R7.2, SSR2.1
unnamed: R6.2, SSR1.1
unnamed: J14.1, U6.4
unnamed: L12.1, U5.1
unnamed: C6.2, U9.6, X1.1
unnamed: C5.1, U9.5, X1.3
unnamed: L2.1, R4.2
unnamed: LED1.C, R8.2
unnamed: R16.2, U8.4
unnamed: J17.2, R11.1
unnamed: R23.1, U11.5, WRITE_ENABLE.P$1
unnamed: J22.2, Q2.3, R25.2
unnamed: F1.2, L4.1
unnamed: J5.2, R17.2
unnamed: J8.1, SSR2.4
unnamed: J8.2, SSR2.3
unnamed: J6.2, SSR1.3
unnamed: J6.1, SSR1.4
unnamed: J9.3, R15.2
unnamed: J9.2, R10.2
unnamed: J2.1, U1.1
unnamed: J3.1, U3.1
unnamed: LED2.C, R12.2
unnamed: LED4.C, R13.2
unnamed: J15.2, R14.1, U7.7
unnamed: J15.3, R14.2, U7.6
unnamed: J15.1, L4.2
NRST: !RESET.P$1, C4.1, S1.A1, U9.7
PB2-BOOT1: R3.1, U9.20
PPM1: J16.22, U2.14
PPM2: J16.19, U2.15
PPM3: J16.16, U2.16
PPM4: J16.13, U2.17
PPM5: J16.10, U2.18
PPM6: J16.7, U2.19
PPM7: J16.4, U2.20
PPM8: J16.1, U2.21
PPM_INPUT: J1.23, J4.1, U6.1, U9.29
RELAY1: R6.1, U9.33
RELAY2: R7.1, U9.32
SAFETY: J17.3, R2.1, U9.41
SERVO_OC_DETECT: U4.3, U9.26
SERVO_PWR_EN: R22.2, U4.4, U9.4
USART1_RX: J7.1, J13.2, U9.31, U$7.1, USART1_RX.P$1
USART1_TX: J13.1, U6.3, U9.30, USART1_TX.P$1
USART2_RX: J21.3, R19.1, U9.13
USART2_TX: J21.2, R9.1, U9.12
USART3_RX: U6.6, U9.22
VDD_3V3: C8.1, C9.1, C10.1, C11.A, J7.3, J12.1, J17.1, LED1.A, LED2.A, LED4.A, U2.1, U2.2, U6.5, U7.3, U9.1, U9.9, U9.24, U9.36, U9.48, U10.2, U10.4, U11.4, VDD_3V3.P$1
VDD_5V: D1.CATHODE, D2.CATHODE, F1.1, J1.1, J1.2, L3.1, U1.5, U3.5, U4.5, U5.4, U5.5, U10.3
VDD_5V_ANALOG: J5.1, L3.2
VDD_SERVO: C1.1, D1.ANODE, L1.2, U2.23, U2.24, U4.1
VDD_SERVO_EXT: J4.2, J14.2, J16.2, J16.5, J16.8, J16.11, J16.14, J16.17, J16.20, J16.23, L1.1
VIN: C7.A, D3.CATHODE, J22.1, L2.2, Q1.4, R25.1, U8.1
VIN_CONTACT: 6-18V.1, J10.1, Q1.1, Q1.2, Q1.5, Q1.6
VOUT: D2.ANODE, D3.ANODE, U8.3

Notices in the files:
PX4FMUv2.4.3.brd:
(c) 2013 mjs/lm/jo
